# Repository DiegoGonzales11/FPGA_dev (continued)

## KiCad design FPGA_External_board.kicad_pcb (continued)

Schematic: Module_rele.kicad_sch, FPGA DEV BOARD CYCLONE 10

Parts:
D1: LED RED; LED_0805_2012Metric
D2: D; D_SOD-323
J1: Conn_01x03_Socket; TerminalBlock_RND_205-00002_1x03_P5.00mm_Horizontal
K1: SANYOU_SRD_Form_C; Relay_SPDT_SANYOU_SRD_Series_Form_C
Q1: CBI 2N2222AU; Transistor NPN 2n2222AU - SOT-89
R3: 500; R_0805_2012Metric_Pad1.20x1.40mm_HandSolder
R4: 1K; R_0805_2012Metric_Pad1.20x1.40mm_HandSolder
U1: Optocoupler_DC_PhotoNPN_AKEC; DIP-4_W7.62mm

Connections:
/Module_rele_1/NA: J1.3, K1.3
/Module_rele_1/NC: J1.1, K1.4
/Module_rele_1/com: J1.2, K1.1
/con_rele_1: D1.1 (K); also elsewhere on the board
GND: Q1.2 (E); also elsewhere on the board
unnamed: D1.2 (A), U1.2
unnamed: D2.2 (A), K1.2, Q1.3 (C)
unnamed: Q1.1 (B), R4.1
unnamed: R3.1, U1.1
unnamed: R4.2, U1.3
VCC: D2.1 (K), K1.5, R3.2, U1.4; also elsewhere on the board

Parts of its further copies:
D3: LED RED; LED_0805_2012Metric
D4: D; D_SOD-323
J2: Conn_01x03_Socket; TerminalBlock_RND_205-00002_1x03_P5.00mm_Horizontal
K2: SANYOU_SRD_Form_C; Relay_SPDT_SANYOU_SRD_Series_Form_C
Q2: CBI 2N2222AU; Transistor NPN 2n2222AU - SOT-89
R5: 500; R_0805_2012Metric_Pad1.20x1.40mm_HandSolder
R6: 1K; R_0805_2012Metric_Pad1.20x1.40mm_HandSolder
U2: Optocoupler_DC_PhotoNPN_AKEC; DIP-4_W7.62mm

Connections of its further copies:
/Module_rele_2/NA: J2.3, K2.3
/Module_rele_2/NC: J2.1, K2.4
/Module_rele_2/com: J2.2, K2.1
/con_rele_2: D3.1 (K); also elsewhere on the board
GND: Q2.2 (E); also elsewhere on the board
unnamed: D3.2 (A), U2.2
unnamed: D4.2 (A), K2.2, Q2.3 (C)
unnamed: Q2.1 (B), R6.1
unnamed: R5.1, U2.1
unnamed: R6.2, U2.3
VCC: D4.1 (K), K2.5, R5.2, U2.4; also elsewhere on the board

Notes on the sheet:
RElE MODULE

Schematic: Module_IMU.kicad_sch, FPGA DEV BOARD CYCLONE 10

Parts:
C14, C15: 100n; C_0805_2012Metric
JP14: SolderJumper_3_Open; SolderJumper-3_P1.3mm_Open_RoundedPad1.0x1.5mm
U10: LSM6DS3; LGA-14_3x2.5mm_P0.5mm_LayoutBorder3x4y

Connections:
+3.3V: C14.2, C15.2, JP14.3 (B), U10.5 (VDDIO), U10.8 (VDD), U10.12 (CS); also elsewhere on the board
/FPGA_I2C_SCL: U10.13 (SCL); also elsewhere on the board
/FPGA_I2C_SDA: U10.14 (SDA); also elsewhere on the board
/con_IMU_int_1: U10.4 (INT1); also elsewhere on the board
/con_IMU_int_2: U10.9 (INT2); also elsewhere on the board
GND: C14.1, C15.1, JP14.1 (A), U10.2 (SDX), U10.3 (SCX), U10.6 (GND), U10.7 (GND); also elsewhere on the board
unnamed: JP14.2 (C), U10.1 (SDO/SA0)

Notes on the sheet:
IMU MODULE

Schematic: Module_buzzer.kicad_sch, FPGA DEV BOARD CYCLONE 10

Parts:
BZ1: Buzzer; Buzzer_12x9.5RM7.6
Q7: CBI 2N2222AU; Transistor NPN 2n2222AU - SOT-89
R19: 1K; R_0805_2012Metric_Pad1.20x1.40mm_HandSolder

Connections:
/con_buzzer: R19.2; also elsewhere on the board
GND: Q7.2 (E); also elsewhere on the board
unnamed: BZ1.2 (-), Q7.3 (C)
unnamed: Q7.1 (B), R19.1
VCC: BZ1.1 (+); also elsewhere on the board

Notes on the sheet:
BUZZER MODULE

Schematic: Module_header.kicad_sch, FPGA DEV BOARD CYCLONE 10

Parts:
J8: Conn_02x15_Top_Bottom; Pin Header Female 2x15 sec123

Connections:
+3.3V: J8.16; also elsewhere on the board
/FPGA_Free_1: J8.4; also elsewhere on the board
/FPGA_Free_2: J8.5; also elsewhere on the board
/FPGA_Free_3: J8.6; also elsewhere on the board
/FPGA_Free_4: J8.7; also elsewhere on the board
/FPGA_Free_5: J8.8; also elsewhere on the board
/FPGA_Free_6: J8.9; also elsewhere on the board
/FPGA_Free_7: J8.10; also elsewhere on the board
/FPGA_Free_8: J8.11; also elsewhere on the board
/FPGA_Free_9: J8.12; also elsewhere on the board
/FPGA_Free_10: J8.13; also elsewhere on the board
/FPGA_Free_11: J8.14; also elsewhere on the board
/FPGA_Free_12: J8.17; also elsewhere on the board
/FPGA_Free_13: J8.18; also elsewhere on the board
/FPGA_Free_14: J8.19; also elsewhere on the board
/FPGA_Free_15: J8.20; also elsewhere on the board
/FPGA_Free_16: J8.21; also elsewhere on the board
/FPGA_Free_17: J8.22; also elsewhere on the board
/FPGA_Free_18: J8.23; also elsewhere on the board
/FPGA_Free_19: J8.24; also elsewhere on the board
/FPGA_Free_20: J8.25; also elsewhere on the board
/FPGA_Free_21: J8.26; also elsewhere on the board
/FPGA_Free_22: J8.27; also elsewhere on the board
/FPGA_Free_23: J8.28; also elsewhere on the board
/FPGA_RX: J8.2; also elsewhere on the board
/FPGA_TX: J8.3; also elsewhere on the board
GND: J8.15, J8.29, J8.30; also elsewhere on the board
VCC: J8.1; also elsewhere on the board

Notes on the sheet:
PIN HEADER MODULE

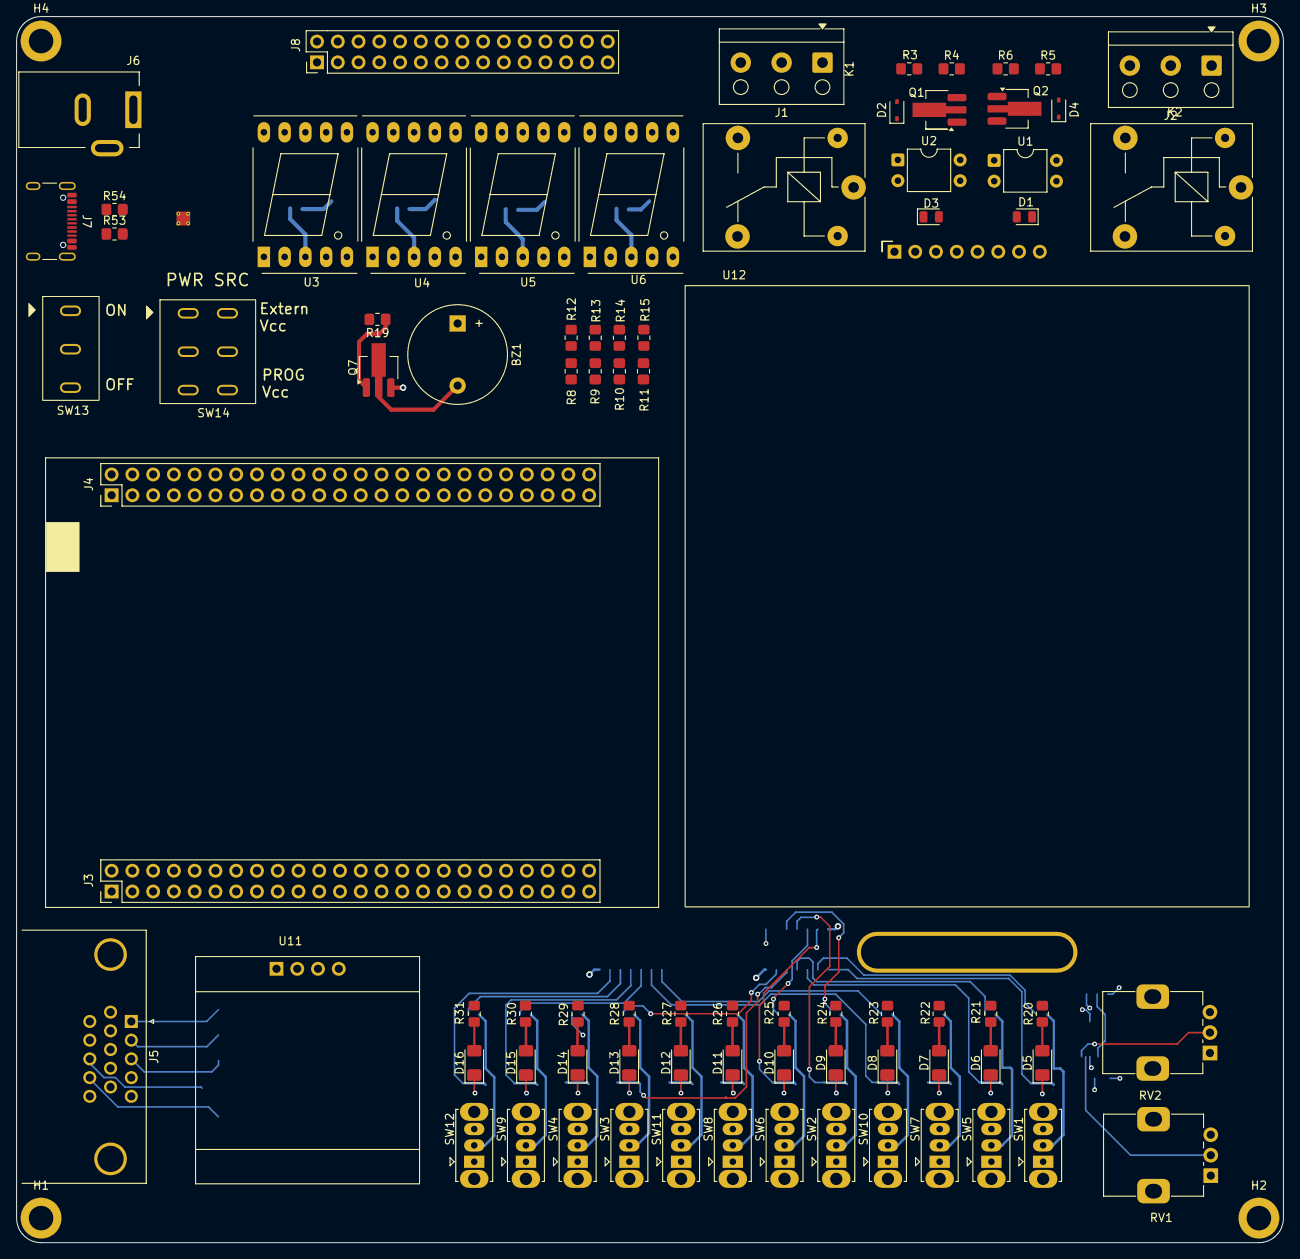
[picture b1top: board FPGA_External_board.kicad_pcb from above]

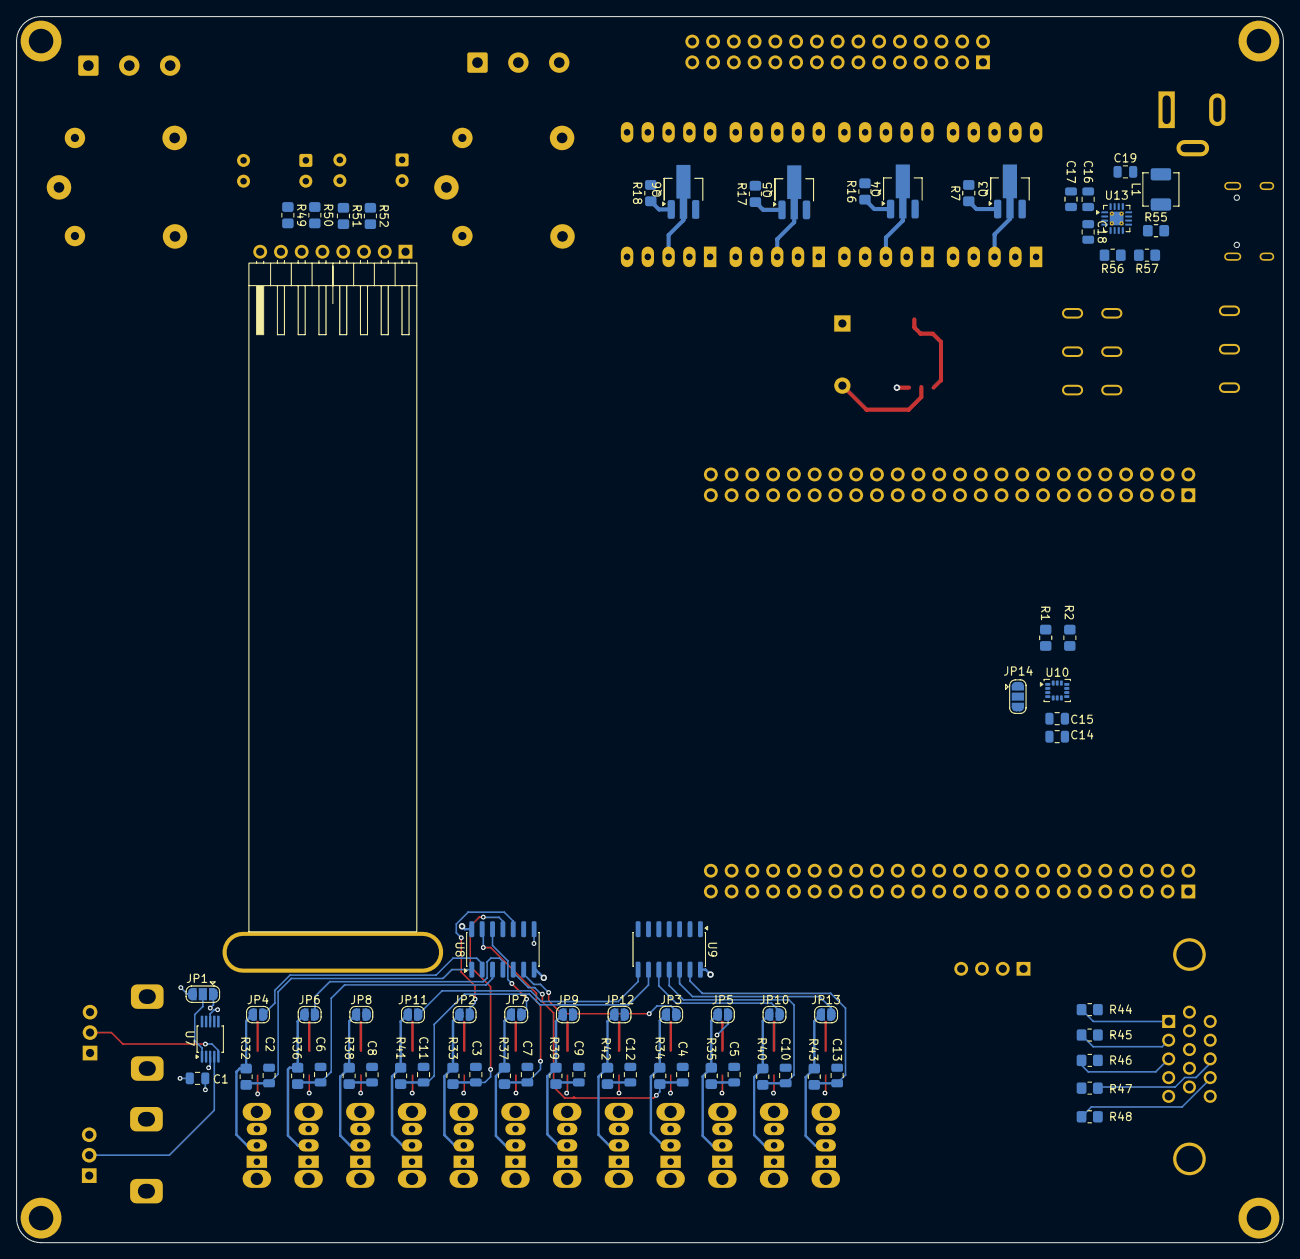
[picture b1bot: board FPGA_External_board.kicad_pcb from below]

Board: 4 copper layers, 155.0 x 150.0 mm, 158 parts (73 on the bottom side), 174 nets.
